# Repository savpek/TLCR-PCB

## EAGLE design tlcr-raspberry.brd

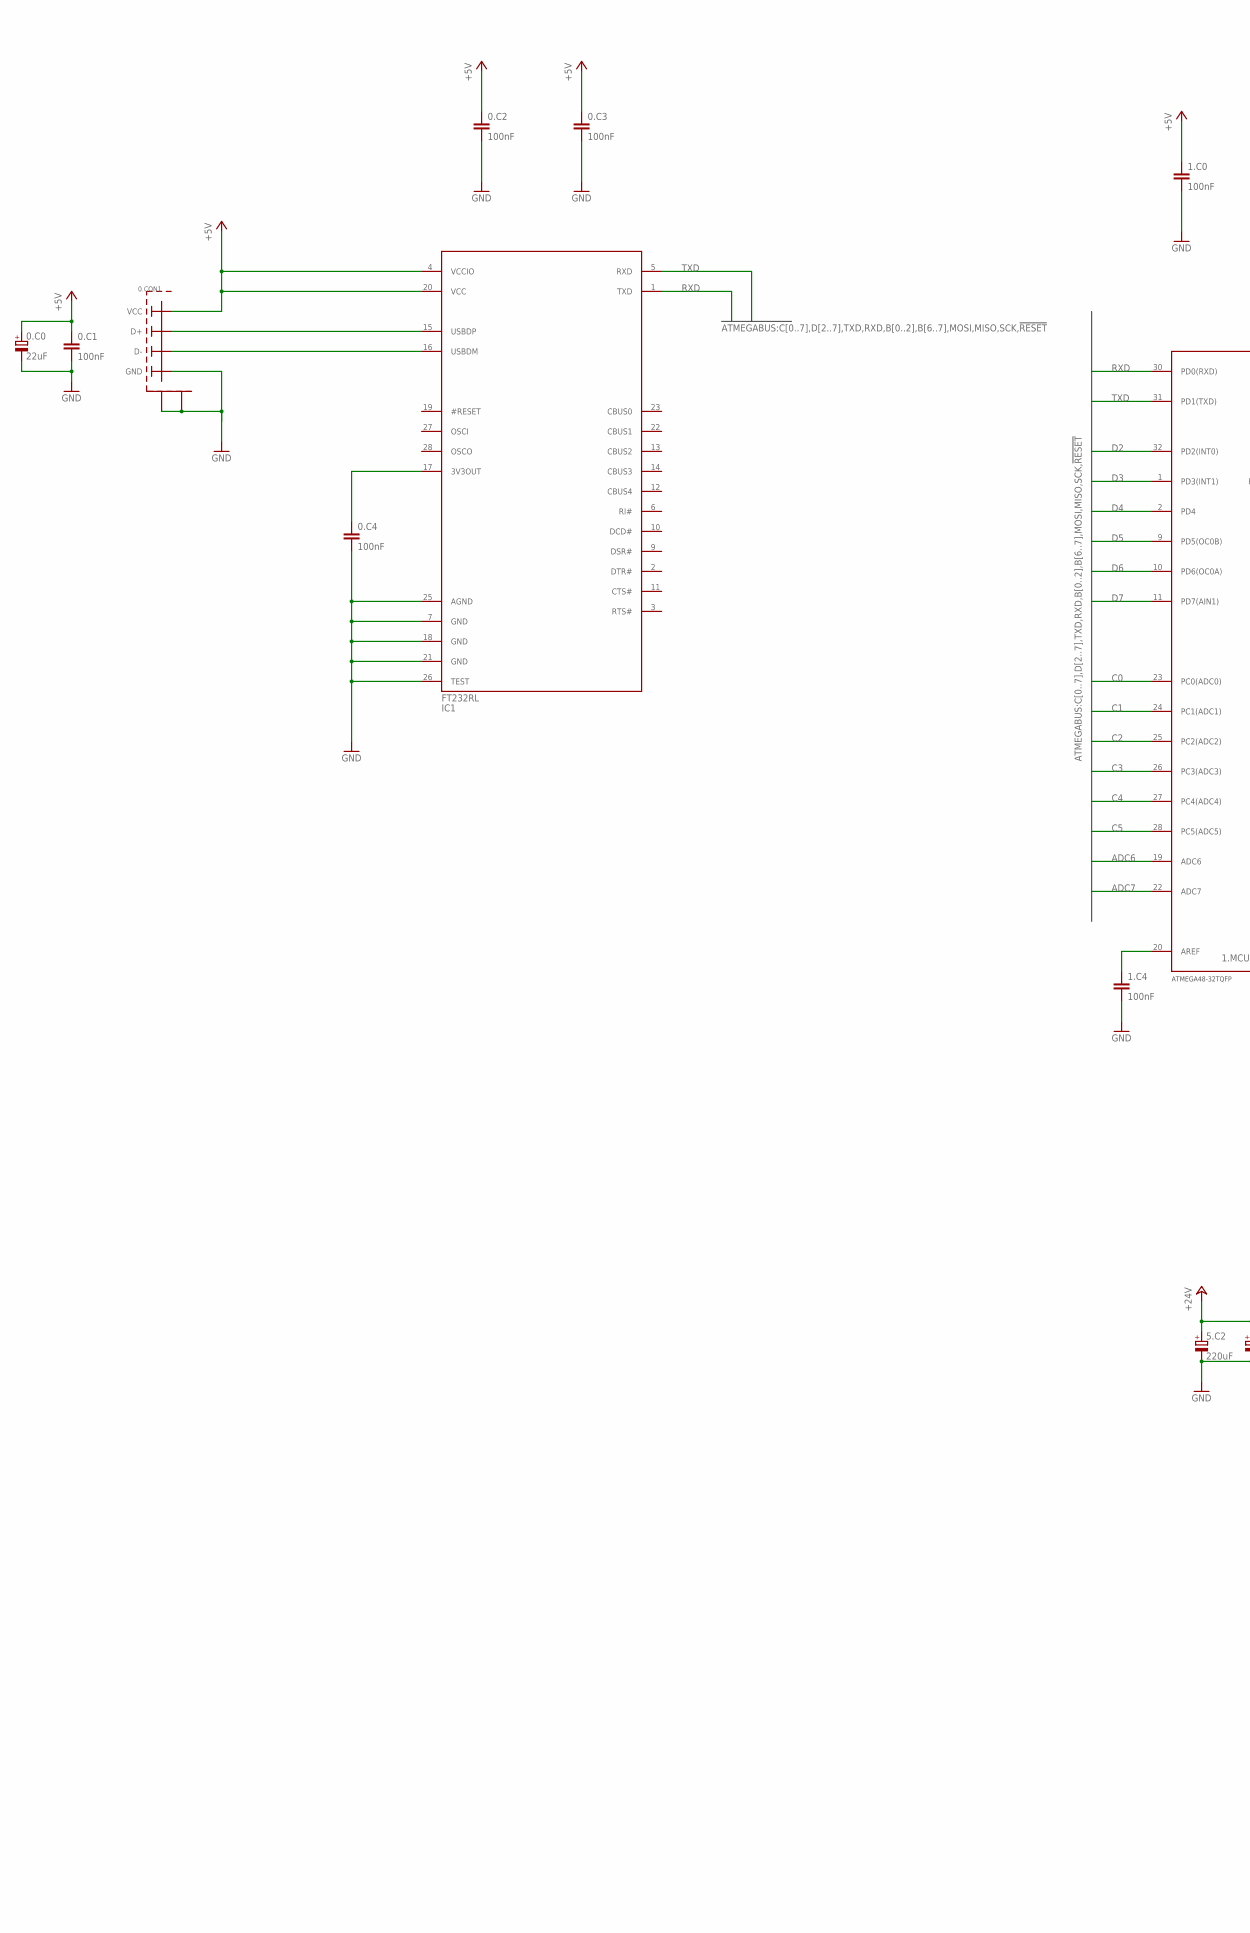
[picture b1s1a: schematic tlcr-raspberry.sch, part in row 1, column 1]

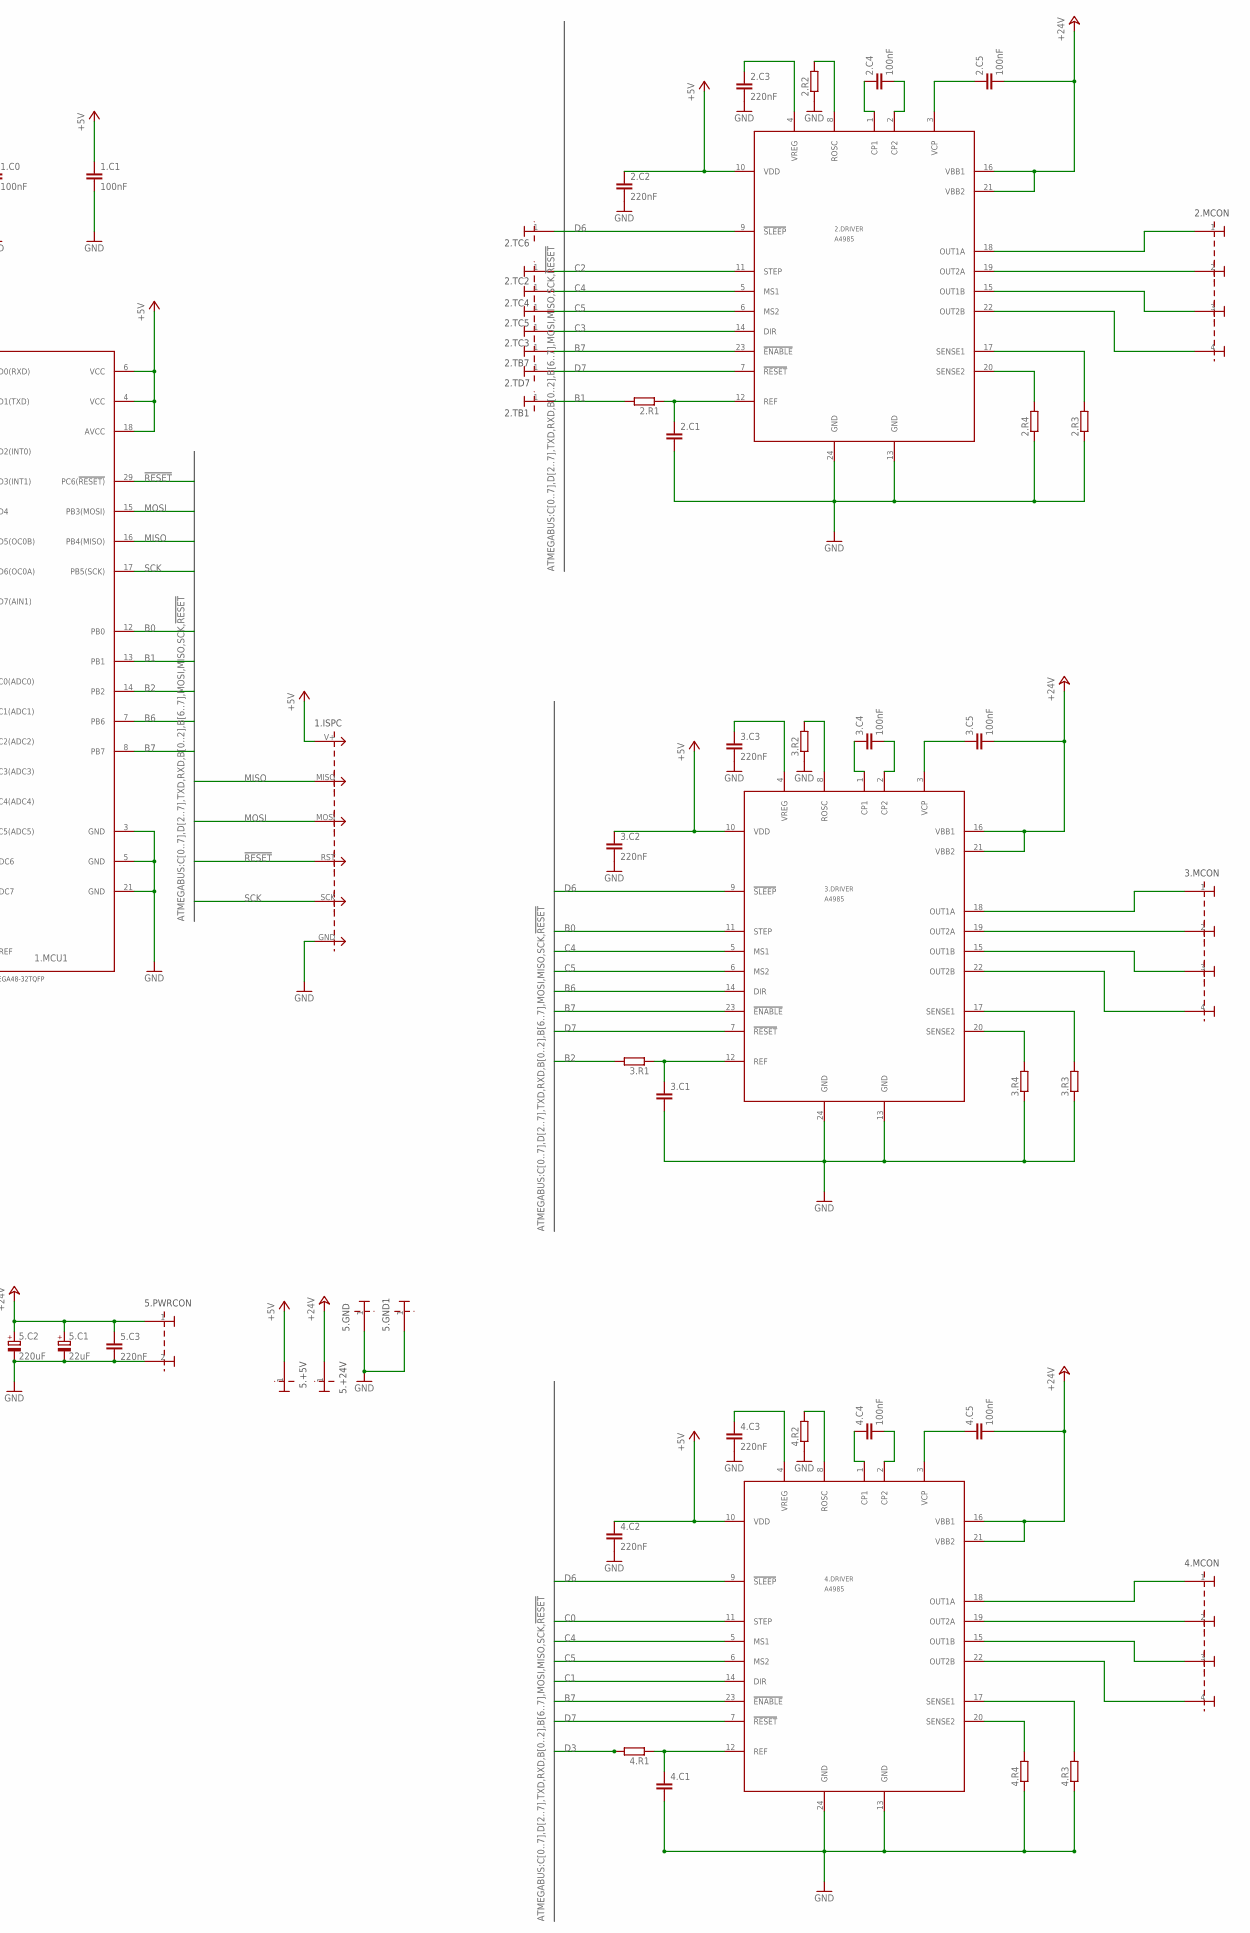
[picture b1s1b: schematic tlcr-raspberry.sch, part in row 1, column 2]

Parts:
0.C0: 22uF; E1.5-5
0.C1, 0.C2, 0.C3, 0.C4, 1.C0, 1.C1, 1.C4, 2.C4, 2.C5, 3.C4, 3.C5, 4.C4, 4.C5: 100nF; C0805
0.CON1: USB-BWUERTH-ELECTRONIC-USB-B; USB-B-THROUGH-HOLE
1.ISPC: CONNECTOR_6PIN2X3_ISP; 2X3_ISP
1.MCU1: ATMEGA48-20PU-32TQFPTQFP32; TQFP32-08
2.C1, 3.C1, 4.C1: C-EUC0805; C0805
2.C2, 2.C3, 3.C2, 3.C3, 4.C2, 4.C3, 5.C3: 220nF; C0805
2.DRIVER, 3.DRIVER, 4.DRIVER: A4985; SSOP24
2.MCON, 3.MCON, 4.MCON: CONNECTOR_4PIN; 1X4_GENERIC
2.R1, 2.R2, 3.R1, 3.R2, 4.R1, 4.R2: R-EU_R0805; R0805
2.R3, 2.R4, 3.R3, 3.R4, 4.R3, 4.R4: R-EU_R2010; R2010
2.TB1, 2.TB7, 2.TC2, 2.TC3, 2.TC4, 2.TC5, 2.TC6, 2.TD7, 5.+5V, 5.+24V, 5.GND, 5.GND1: CONNECTOR_1PIN1X1_HEADER; 1X1_GENERIC
5.C1: 22uF; 140CLH-0810
5.C2: 220uF; 140CLH-0810
5.PWRCON: CONNECTOR_2PIN1X2_WIRE; 1X2_WIRE
IC1: FT232RL; SSOP28

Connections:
!RESET: 1.ISPC.RST, 1.MCU1.29 (PC6(!RESET))
+5V: 0.C0.+, 0.C1.1, 0.C2.1, 0.C3.1, 0.CON1.VCC, 1.C0.1, 1.C1.1, 1.ISPC.V+, 1.MCU1.4 (VCC), 1.MCU1.6 (VCC), 1.MCU1.18 (AVCC), 2.C2.1, 2.DRIVER.10 (VDD), 3.C2.1, 3.DRIVER.10 (VDD), 4.C2.1, 4.DRIVER.10 (VDD), 5.+5V.1, IC1.4 (VCCIO), IC1.20 (VCC)
+24V: 2.C5.2, 2.DRIVER.16 (VBB1), 2.DRIVER.21 (VBB2), 3.C5.2, 3.DRIVER.16 (VBB1), 3.DRIVER.21 (VBB2), 4.C5.2, 4.DRIVER.16 (VBB1), 4.DRIVER.21 (VBB2), 5.+24V.1, 5.C1.+, 5.C2.+, 5.C3.1, 5.PWRCON.1
ADC6: 1.MCU1.19 (ADC6)
ADC7: 1.MCU1.22 (ADC7)
B0: 1.MCU1.12 (PB0), 3.DRIVER.11 (STEP)
B1: 1.MCU1.13 (PB1), 2.R1.2, 2.TB1.1
B2: 1.MCU1.14 (PB2), 3.R1.2
B6: 1.MCU1.7 (PB6), 3.DRIVER.14 (DIR)
B7: 1.MCU1.8 (PB7), 2.DRIVER.23 (!ENABLE), 2.TB7.1, 3.DRIVER.23 (!ENABLE), 4.DRIVER.23 (!ENABLE)
C0: 1.MCU1.23 (PC0(ADC0)), 4.DRIVER.11 (STEP)
C1: 1.MCU1.24 (PC1(ADC1)), 4.DRIVER.14 (DIR)
C2: 1.MCU1.25 (PC2(ADC2)), 2.DRIVER.11 (STEP), 2.TC2.1
C3: 1.MCU1.26 (PC3(ADC3)), 2.DRIVER.14 (DIR), 2.TC3.1
C4: 1.MCU1.27 (PC4(ADC4)), 2.DRIVER.5 (MS1), 2.TC4.1, 3.DRIVER.5 (MS1), 4.DRIVER.5 (MS1)
C5: 1.MCU1.28 (PC5(ADC5)), 2.DRIVER.6 (MS2), 2.TC5.1, 3.DRIVER.6 (MS2), 4.DRIVER.6 (MS2)
D2: 1.MCU1.32 (PD2(INT0))
D3: 1.MCU1.1 (PD3(INT1)), 4.R1.2
D4: 1.MCU1.2 (PD4)
D5: 1.MCU1.9 (PD5(OC0B))
D6: 1.MCU1.10 (PD6(OC0A)), 2.DRIVER.9 (!SLEEP), 2.TC6.1, 3.DRIVER.9 (!SLEEP), 4.DRIVER.9 (!SLEEP)
D7: 1.MCU1.11 (PD7(AIN1)), 2.DRIVER.7 (!RESET), 2.TD7.1, 3.DRIVER.7 (!RESET), 4.DRIVER.7 (!RESET)
GND: 0.C0.-, 0.C1.2, 0.C2.2, 0.C3.2, 0.C4.2, 0.CON1.GND, 0.CON1.SHIELD, 0.CON1.SHIELD@2 (SHIELD), 1.C0.2, 1.C1.2, 1.C4.2, 1.ISPC.GND, 1.MCU1.3 (GND), 1.MCU1.5 (GND), 1.MCU1.21 (GND), 2.C1.2, 2.C2.2, 2.C3.2, 2.DRIVER.13 (GND), 2.DRIVER.24 (GND), 2.R2.1, 2.R3.1, 2.R4.1, 3.C1.2, 3.C2.2, 3.C3.2, 3.DRIVER.13 (GND), 3.DRIVER.24 (GND), 3.R2.1, 3.R3.1, 3.R4.1, 4.C1.2, 4.C2.2, 4.C3.2, 4.DRIVER.13 (GND), 4.DRIVER.24 (GND), 4.R2.1, 4.R3.1, 4.R4.1, 5.C1.-, 5.C2.-, 5.C3.2, 5.GND.1, 5.GND1.1, 5.PWRCON.2, IC1.7 (GND), IC1.18 (GND), IC1.21 (GND), IC1.25 (AGND), IC1.26 (TEST)
MISO: 1.ISPC.MISO, 1.MCU1.16 (PB4(MISO))
MOSI: 1.ISPC.MOSI, 1.MCU1.15 (PB3(MOSI))
unnamed: 1.C4.1, 1.MCU1.20 (AREF)
unnamed: 2.C3.1, 2.DRIVER.4 (VREG)
unnamed: 0.CON1.D+, IC1.15 (USBDP)
unnamed: 0.CON1.D-, IC1.16 (USBDM)
unnamed: 2.C4.1, 2.DRIVER.1 (CP1)
unnamed: 2.C4.2, 2.DRIVER.2 (CP2)
unnamed: 0.C4.1, IC1.17 (3V3OUT)
unnamed: 2.C5.1, 2.DRIVER.3 (VCP)
unnamed: 3.C3.1, 3.DRIVER.4 (VREG)
unnamed: 2.DRIVER.18 (OUT1A), 2.MCON.1
unnamed: 2.DRIVER.19 (OUT2A), 2.MCON.2
unnamed: 2.DRIVER.15 (OUT1B), 2.MCON.3
unnamed: 2.DRIVER.22 (OUT2B), 2.MCON.4
unnamed: 2.DRIVER.17 (SENSE1), 2.R3.2
unnamed: 2.DRIVER.20 (SENSE2), 2.R4.2
unnamed: 3.C4.1, 3.DRIVER.1 (CP1)
unnamed: 3.C4.2, 3.DRIVER.2 (CP2)
unnamed: 2.DRIVER.8 (ROSC), 2.R2.2
unnamed: 3.C5.1, 3.DRIVER.3 (VCP)
unnamed: 3.DRIVER.18 (OUT1A), 3.MCON.1
unnamed: 3.DRIVER.19 (OUT2A), 3.MCON.2
unnamed: 3.DRIVER.15 (OUT1B), 3.MCON.3
unnamed: 3.DRIVER.22 (OUT2B), 3.MCON.4
unnamed: 3.DRIVER.17 (SENSE1), 3.R3.2
unnamed: 3.DRIVER.20 (SENSE2), 3.R4.2
unnamed: 3.DRIVER.8 (ROSC), 3.R2.2
unnamed: 4.C3.1, 4.DRIVER.4 (VREG)
unnamed: 4.C4.1, 4.DRIVER.1 (CP1)
unnamed: 4.C4.2, 4.DRIVER.2 (CP2)
unnamed: 4.C5.1, 4.DRIVER.3 (VCP)
unnamed: 4.DRIVER.18 (OUT1A), 4.MCON.1
unnamed: 4.DRIVER.19 (OUT2A), 4.MCON.2
unnamed: 4.DRIVER.15 (OUT1B), 4.MCON.3
unnamed: 4.DRIVER.22 (OUT2B), 4.MCON.4
unnamed: 4.DRIVER.17 (SENSE1), 4.R3.2
unnamed: 4.DRIVER.20 (SENSE2), 4.R4.2
unnamed: 4.DRIVER.8 (ROSC), 4.R2.2
unnamed: 3.C1.1, 3.DRIVER.12 (REF), 3.R1.1
unnamed: 4.C1.1, 4.DRIVER.12 (REF), 4.R1.1
unnamed: 2.C1.1, 2.DRIVER.12 (REF), 2.R1.1
RXD: 1.MCU1.30 (PD0(RXD)), IC1.1 (TXD)
SCK: 1.ISPC.SCK, 1.MCU1.17 (PB5(SCK))
TXD: 1.MCU1.31 (PD1(TXD)), IC1.5 (RXD)

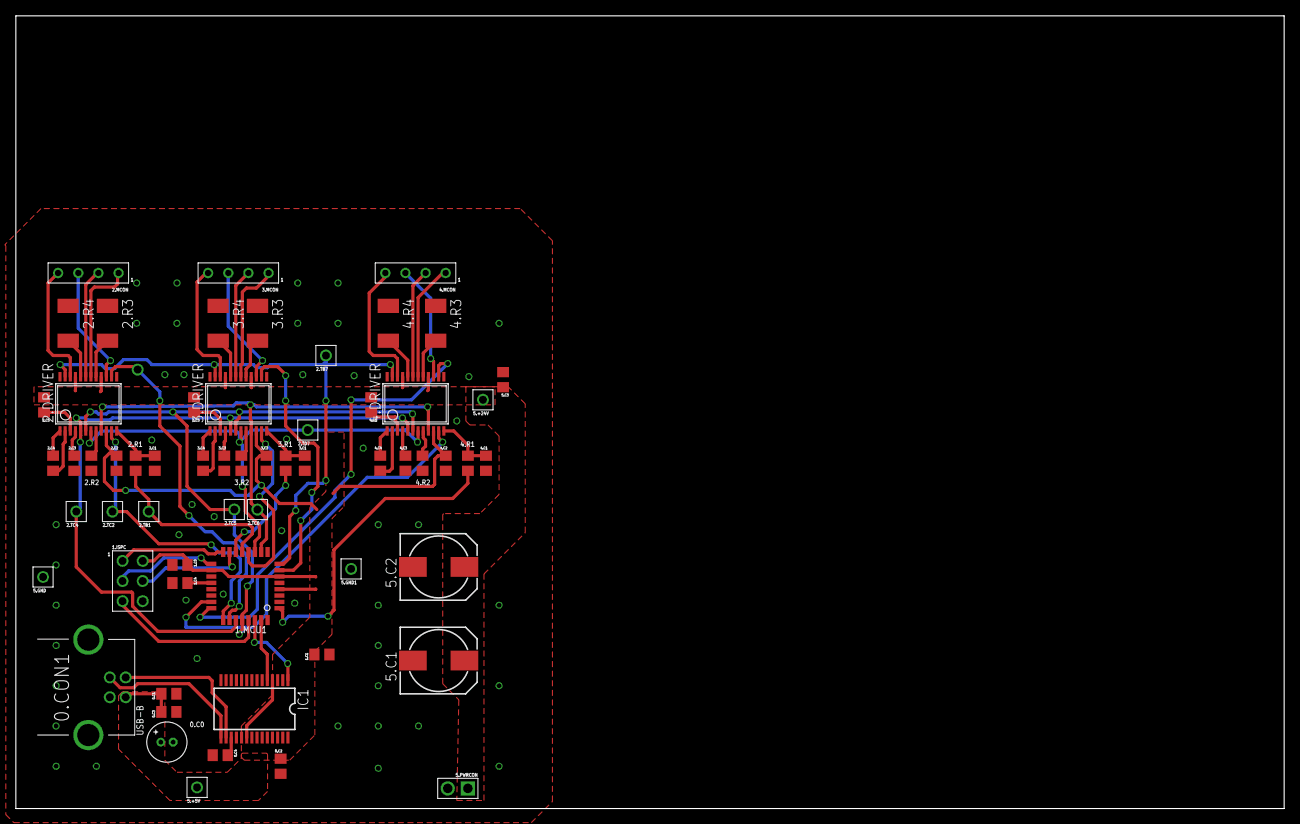
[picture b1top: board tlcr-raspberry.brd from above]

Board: 2 copper layers, 160.0 x 100.0 mm, 61 parts (1 on the bottom side), 63 nets.

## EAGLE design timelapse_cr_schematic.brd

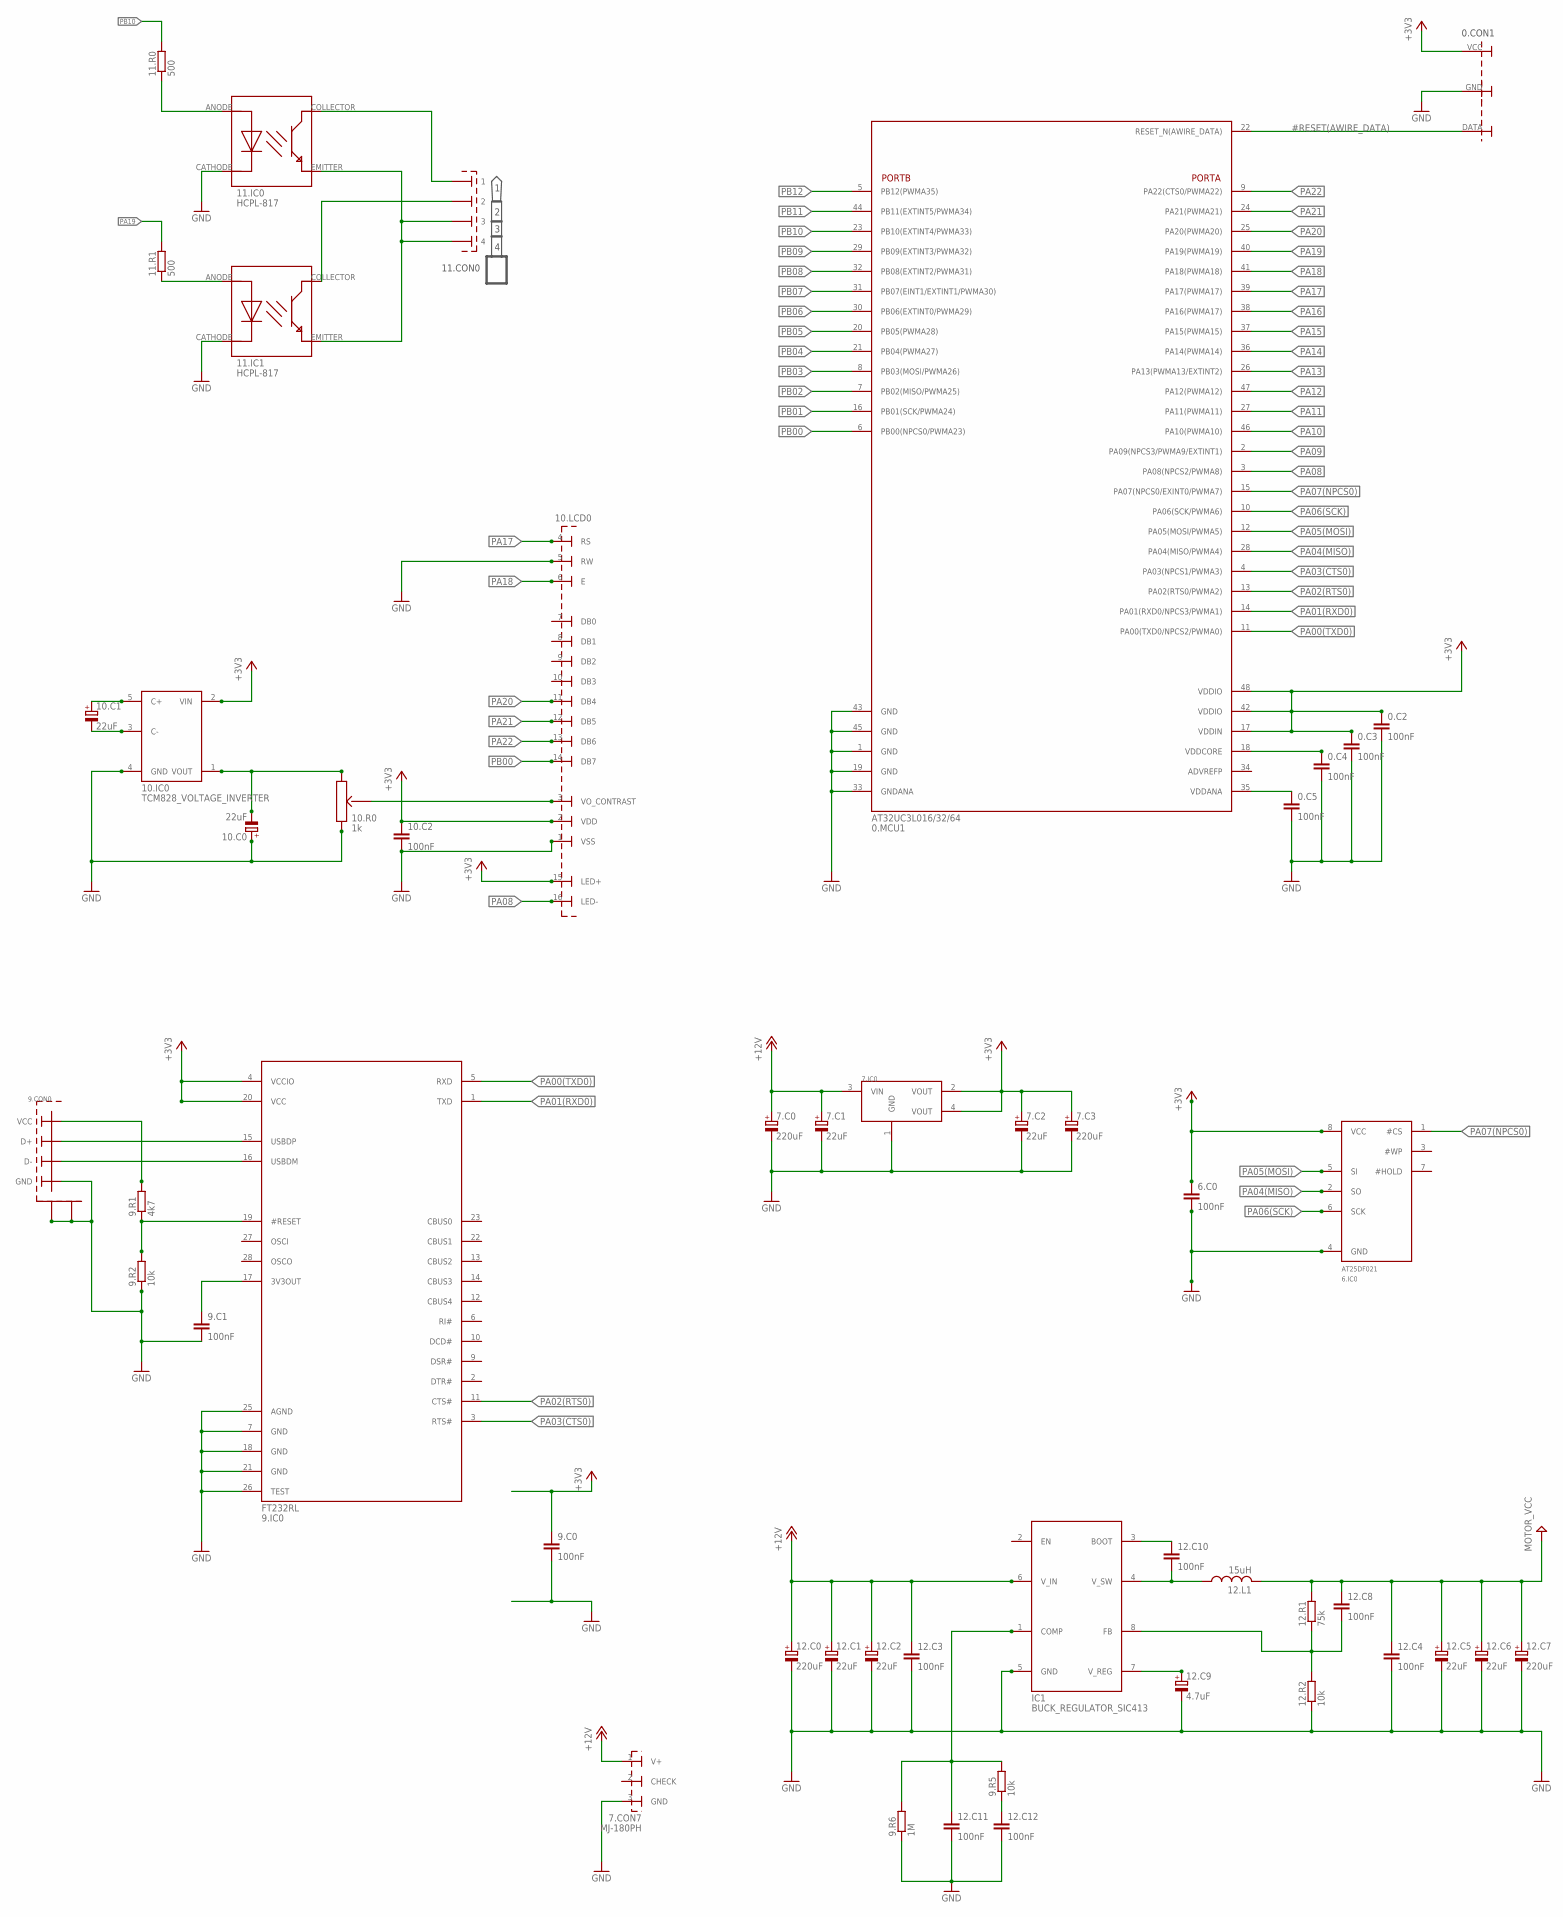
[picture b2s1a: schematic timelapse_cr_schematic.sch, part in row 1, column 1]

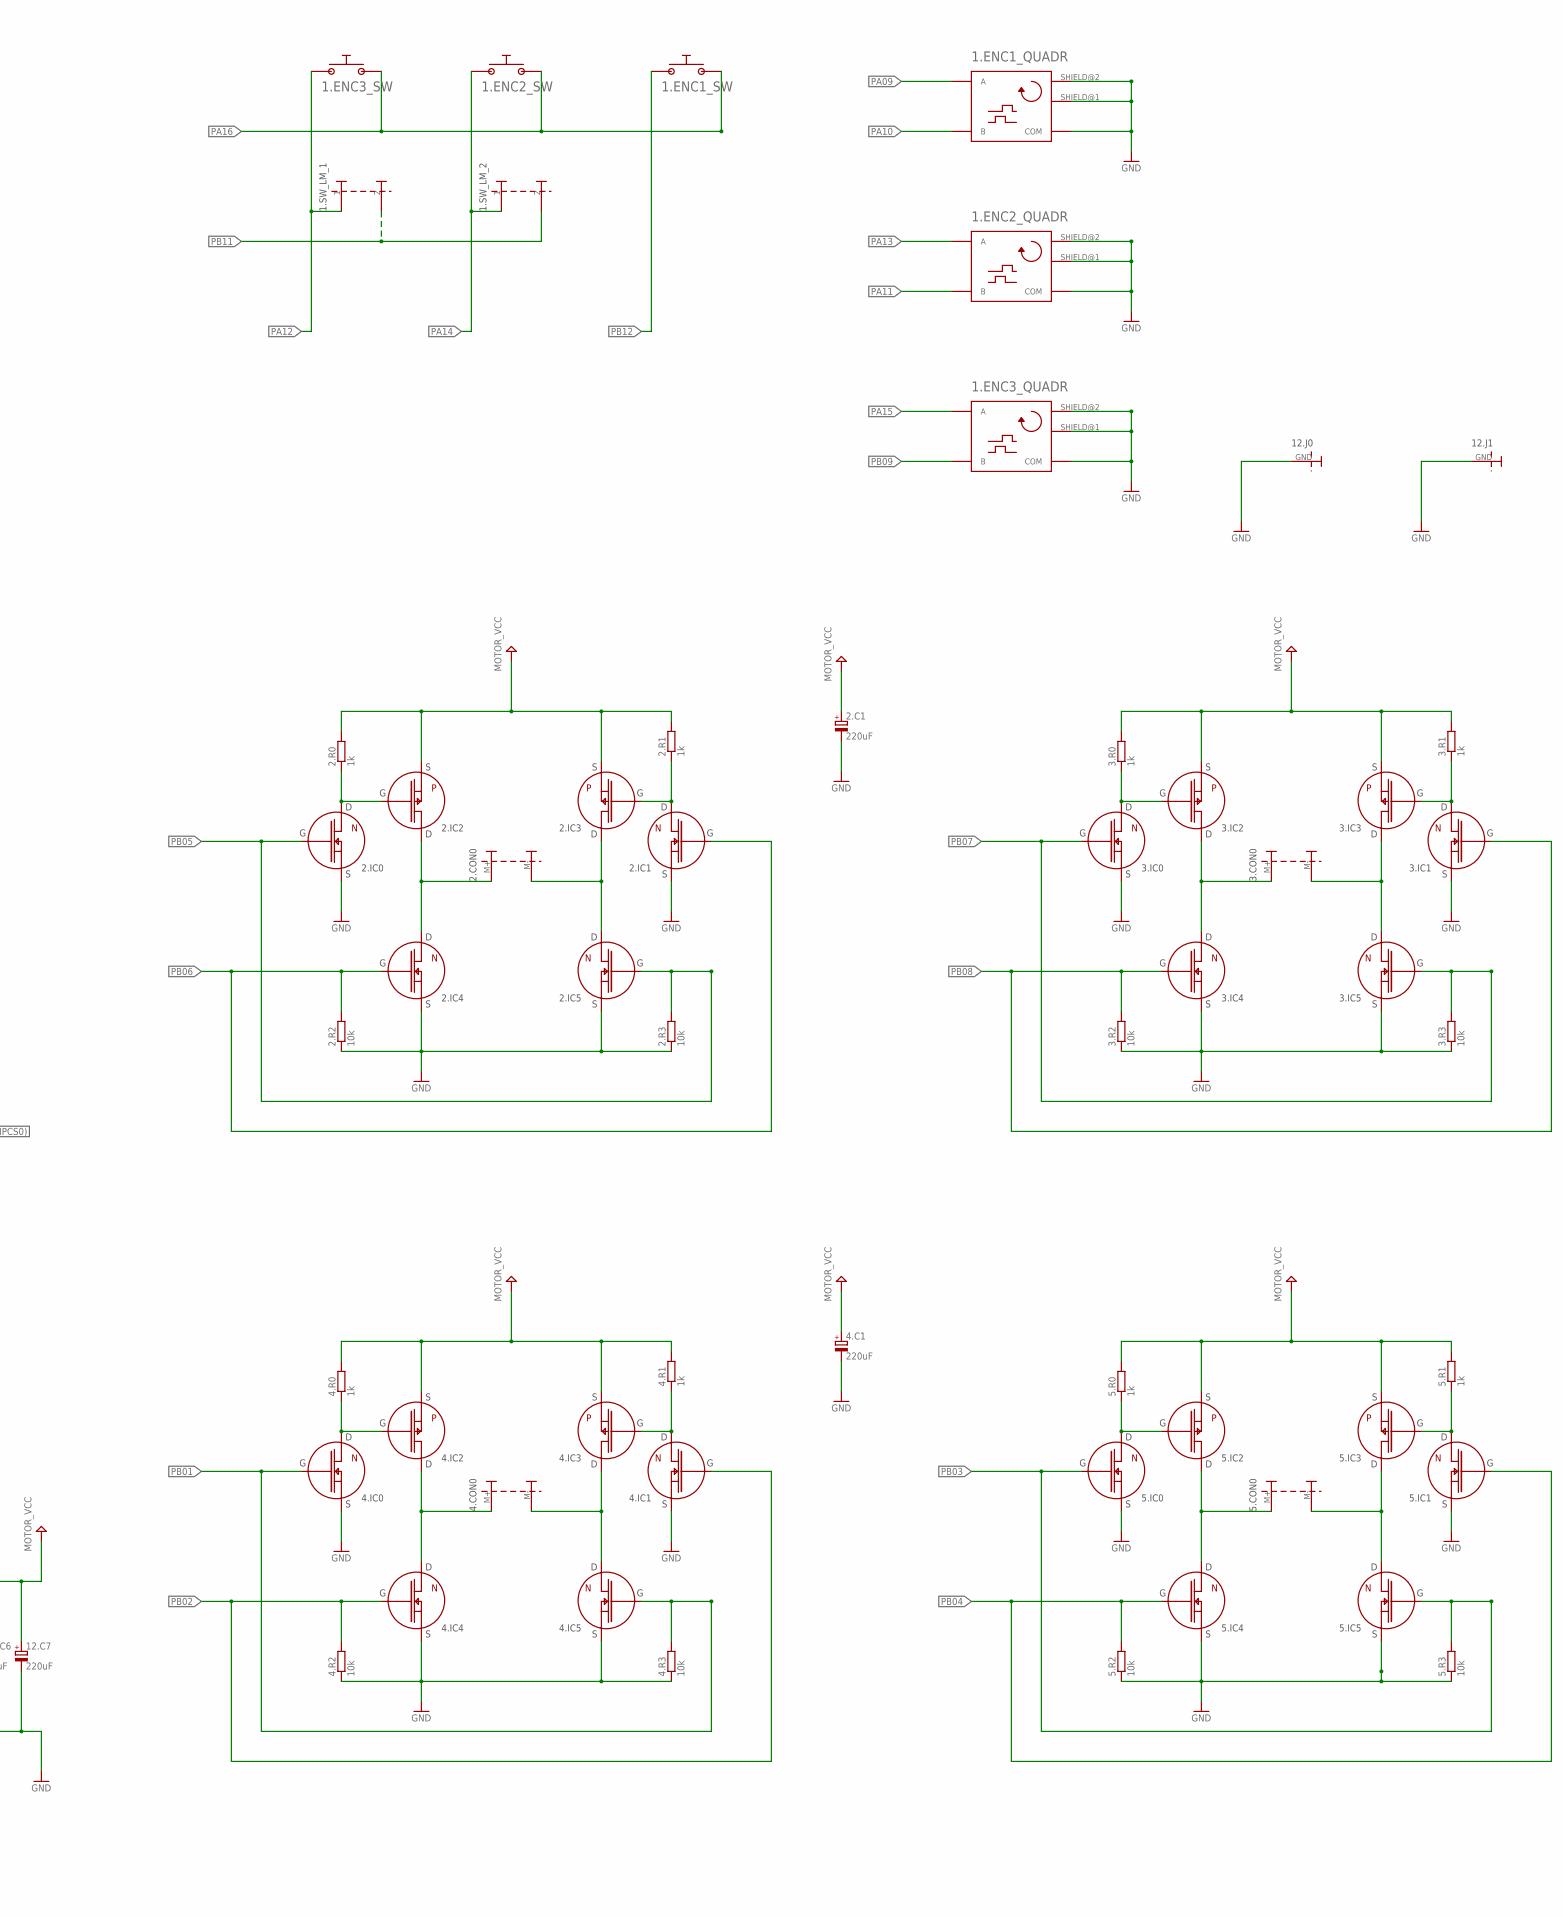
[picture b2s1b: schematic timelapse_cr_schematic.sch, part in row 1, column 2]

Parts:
0.C2, 0.C3, 0.C4, 0.C5, 6.C0, 9.C0, 9.C1, 10.C2, 12.C3, 12.C4, 12.C8, 12.C10, 12.C11, 12.C12: 100nF; C0805
0.CON1: CONNECTOR_3PINAWIRE; 1X3_AWIRE
0.MCU1: AT32UCL016/32/64_TQFP48; TQFP48
1.ENC1, 1.ENC2, 1.ENC3: ENCODER_QUADRATE_WITH_BUTTON_ENCODER_PEC11-4XXXF-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; ENCODER_PEC11-4XXXF-SXXXX
1.SW_LM_1, 1.SW_LM_2: CONNECTOR_2PIN; 1X2_WIRE
2.C1, 4.C1, 7.C0, 7.C3, 12.C0, 12.C7: 220uF; E3,5-8
2.CON0, 3.CON0, 4.CON0, 5.CON0: CONNECTOR_2PIN1X2_MOTOR_COIL; 1X2_MOTOR_COIL_CONNECTOR
2.IC0, 2.IC1, 3.IC0, 3.IC1, 4.IC0, 4.IC1, 5.IC0, 5.IC1: N_MOSFET_TSM2N7002; SOT23
2.IC2, 2.IC3, 3.IC2, 3.IC3, 4.IC2, 4.IC3, 5.IC2, 5.IC3: P_MOSFET_NX2301P; SOT23
2.IC4, 2.IC5, 3.IC4, 3.IC5, 4.IC4, 4.IC5, 5.IC4, 5.IC5: N_MOSFET_PMV16UN; SOT23
2.R0, 2.R1, 3.R0, 3.R1, 4.R0, 4.R1, 5.R0, 5.R1: 1k; R0805
2.R2, 2.R3, 3.R2, 3.R3, 4.R2, 4.R3, 5.R2, 5.R3, 9.R2, 9.R5, 12.R2: 10k; R0805
6.IC0: FLASH_AT25DF021_SO8; SO8
7.C1, 7.C2, 10.C0, 10.C1, 12.C1, 12.C2, 12.C5, 12.C6: 22uF; E1.5-5
7.CON7: MJ-180PH
7.IC0: REGULATOR_AP1117E33G-13; SOT223
9.CON0: USB-BWUERTH-ELECTRONIC-USB-B; USB-B-THROUGH-HOLE
9.IC0: FT232RL; SSOP28
9.R1: 4k7; R0805
9.R6: 1M; R0805
10.IC0: TCM828_VOLTAGE_INVERTER; SOT23-5L
10.LCD0: LCD_WITH_COMMON_INTERFACE_FDCC0802C-NSWBBH-91LE; LCD_FDCC0802C-NSWBBH-91LE
10.R0: 1k; CT6V
11.CON0: 2.5MM-JACK-STEREO-CONNECTOR; PSG01539
11.IC0, 11.IC1: HCPL-817; HPCL-817
11.R0, 11.R1: 500; R0805
12.C9: 4.7uF; E1.5-5
12.J0, 12.J1: CONNECTOR_1PINGND_PIN; 1X1_GND_PIN
12.L1: 15uH; INDUCTOR_MCBFS7330
12.R1: 75k; R0805
IC1: BUCK_REGULATOR_SIC413; SO8

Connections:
#RESET(AWIRE_DATA): 0.CON1.DATA, 0.MCU1.22 (RESET_N(AWIRE_DATA))
+3V3: 0.C2.1, 0.C3.1, 0.CON1.VCC, 0.MCU1.17 (VDDIN), 0.MCU1.42 (VDDIO), 0.MCU1.48 (VDDIO), 6.C0.1, 6.IC0.8 (VCC), 7.C2.+, 7.C3.+, 7.IC0.2 (VOUT), 7.IC0.4 (VOUT), 9.C0.1, 9.IC0.4 (VCCIO), 9.IC0.20 (VCC), 10.C2.1, 10.IC0.2 (VIN), 10.LCD0.2 (VDD), 10.LCD0.15 (LED+)
+12V: 7.C0.+, 7.C1.+, 7.CON7.1 (V+), 7.IC0.3 (VIN), 12.C0.+, 12.C1.+, 12.C2.+, 12.C3.1, IC1.6 (V_IN)
GND: 0.C2.2, 0.C3.2, 0.C4.2, 0.C5.2, 0.CON1.GND, 0.MCU1.1 (GND), 0.MCU1.19 (GND), 0.MCU1.33 (GNDANA), 0.MCU1.43 (GND), 0.MCU1.45 (GND), 1.ENC1.COMMON (COM), 1.ENC1.SHIELD@1 (SHIELD), 1.ENC1.SHIELD@2 (SHIELD), 1.ENC2.COMMON (COM), 1.ENC2.SHIELD@1 (SHIELD), 1.ENC2.SHIELD@2 (SHIELD), 1.ENC3.COMMON (COM), 1.ENC3.SHIELD@1 (SHIELD), 1.ENC3.SHIELD@2 (SHIELD), 2.C1.-, 2.IC0.2 (S), 2.IC1.2 (S), 2.IC4.2 (S), 2.IC5.2 (S), 2.R2.1, 2.R3.1, 3.IC0.2 (S), 3.IC1.2 (S), 3.IC4.2 (S), 3.IC5.2 (S), 3.R2.1, 3.R3.1, 4.C1.-, 4.IC0.2 (S), 4.IC1.2 (S), 4.IC4.2 (S), 4.IC5.2 (S), 4.R2.1, 4.R3.1, 5.IC0.2 (S), 5.IC1.2 (S), 5.IC4.2 (S), 5.IC5.2 (S), 5.R2.1, 5.R3.1, 6.C0.2, 6.IC0.4 (GND), 7.C0.-, 7.C1.-, 7.C2.-, 7.C3.-, 7.CON7.3 (GND), 7.IC0.1 (GND), 9.C0.2, 9.C1.2, 9.CON0.GND, 9.CON0.SHIELD, 9.CON0.SHIELD@2 (SHIELD), 9.IC0.7 (GND), 9.IC0.18 (GND), 9.IC0.21 (GND), 9.IC0.25 (AGND), 9.IC0.26 (TEST), 9.R2.1, 9.R6.1, 10.C0.+, 10.C2.2, 10.IC0.4 (GND), 10.LCD0.1 (VSS), 10.LCD0.5 (RW), 10.R0.3, 11.IC0.CATHODE, 11.IC1.CATHODE, 12.C0.-, 12.C1.-, 12.C2.-, 12.C3.2, 12.C4.2, 12.C5.-, 12.C6.-, 12.C7.-, 12.C9.-, 12.C11.2, 12.C12.2, 12.J0.GND, 12.J1.GND, 12.R2.1, IC1.5 (GND)
MOTOR_VCC: 2.C1.+, 2.IC2.2 (S), 2.IC3.2 (S), 2.R0.2, 2.R1.2, 3.IC2.2 (S), 3.IC3.2 (S), 3.R0.2, 3.R1.2, 4.C1.+, 4.IC2.2 (S), 4.IC3.2 (S), 4.R0.2, 4.R1.2, 5.IC2.2 (S), 5.IC3.2 (S), 5.R0.2, 5.R1.2, 12.C4.1, 12.C5.+, 12.C6.+, 12.C7.+, 12.C8.1, 12.L1.P$2 (2), 12.R1.2
unnamed: 9.C1.1, 9.IC0.17 (3V3OUT)
unnamed: 2.IC0.3 (D), 2.IC2.1 (G), 2.R0.1
unnamed: 9.CON0.D-, 9.IC0.16 (USBDM)
unnamed: 9.CON0.D+, 9.IC0.15 (USBDP)
unnamed: 9.CON0.VCC, 9.R1.2
unnamed: 9.IC0.19 (#RESET), 9.R1.1, 9.R2.2
unnamed: 3.IC0.3 (D), 3.IC2.1 (G), 3.R0.1
unnamed: 2.IC1.3 (D), 2.IC3.1 (G), 2.R1.1
unnamed: 2.CON0.M-, 2.IC3.3 (D), 2.IC5.3 (D)
unnamed: 2.CON0.M+, 2.IC2.3 (D), 2.IC4.3 (D)
unnamed: 3.IC1.3 (D), 3.IC3.1 (G), 3.R1.1
unnamed: 3.CON0.M-, 3.IC3.3 (D), 3.IC5.3 (D)
unnamed: 10.LCD0.3 (VO_CONTRAST), 10.R0.2
unnamed: 3.CON0.M+, 3.IC2.3 (D), 3.IC4.3 (D)
unnamed: 11.CON0.1 (4), 11.CON0.4 (3), 11.IC0.EMITTER, 11.IC1.EMITTER
unnamed: 10.C1.+, 10.IC0.5 (C+)
unnamed: 10.C1.-, 10.IC0.3 (C-)
unnamed: 4.IC0.3 (D), 4.IC2.1 (G), 4.R0.1
unnamed: 4.IC1.3 (D), 4.IC3.1 (G), 4.R1.1
unnamed: 4.CON0.M-, 4.IC3.3 (D), 4.IC5.3 (D)
unnamed: 4.CON0.M+, 4.IC2.3 (D), 4.IC4.3 (D)
unnamed: 9.R5.2, 9.R6.2, 12.C11.1, IC1.1 (COMP)
unnamed: 10.C0.-, 10.IC0.1 (VOUT), 10.R0.1
unnamed: 5.IC0.3 (D), 5.IC2.1 (G), 5.R0.1
unnamed: 5.IC1.3 (D), 5.IC3.1 (G), 5.R1.1
unnamed: 5.CON0.M-, 5.IC3.3 (D), 5.IC5.3 (D)
unnamed: 5.CON0.M+, 5.IC2.3 (D), 5.IC4.3 (D)
unnamed: 0.C4.1, 0.MCU1.18 (VDDCORE)
unnamed: 12.C10.1, IC1.3 (BOOT)
unnamed: 12.C8.2, 12.R1.1, 12.R2.2, IC1.8 (FB)
unnamed: 11.CON0.3 (1), 11.IC0.COLLECTOR
unnamed: 12.C10.2, 12.L1.P$1 (1), IC1.4 (V_SW)
unnamed: 9.R5.1, 12.C12.1
unnamed: 11.CON0.2, 11.IC1.COLLECTOR
unnamed: 0.C5.1, 0.MCU1.35 (VDDANA)
unnamed: 12.C9.+, IC1.7 (V_REG)
unnamed: 11.IC0.ANODE, 11.R0.1
unnamed: 11.IC1.ANODE, 11.R1.1
PA00(TXD0): 0.MCU1.11 (PA00(TXD0/NPCS2/PWMA0)), 9.IC0.5 (RXD)
PA01(RXD0): 0.MCU1.14 (PA01(RXD0/NPCS3/PWMA1)), 9.IC0.1 (TXD)
PA02(RTS0): 0.MCU1.13 (PA02(RTS0/PWMA2)), 9.IC0.11 (CTS#)
PA03(CTS0): 0.MCU1.4 (PA03(NPCS1/PWMA3)), 9.IC0.3 (RTS#)
PA04(MISO): 0.MCU1.28 (PA04(MISO/PWMA4)), 6.IC0.2 (SO)
PA05(MOSI): 0.MCU1.12 (PA05(MOSI/PWMA5)), 6.IC0.5 (SI)
PA06(SCK): 0.MCU1.10 (PA06(SCK/PWMA6)), 6.IC0.6 (SCK)
PA07(NPCS0): 0.MCU1.15 (PA07(NPCS0/EXINT0/PWMA7)), 6.IC0.1 (#CS)
PA08: 0.MCU1.3 (PA08(NPCS2/PWMA8)), 10.LCD0.16 (LED-)
PA09: 0.MCU1.2 (PA09(NPCS3/PWMA9/EXTINT1)), 1.ENC1.A
PA10: 0.MCU1.46 (PA10(PWMA10)), 1.ENC1.B
PA11: 0.MCU1.27 (PA11(PWMA11)), 1.ENC2.B
PA12: 0.MCU1.47 (PA12(PWMA12)), 1.ENC3.SW1, 1.SW_LM_1.1
PA13: 0.MCU1.26 (PA13(PWMA13/EXTINT2)), 1.ENC2.A
PA14: 0.MCU1.36 (PA14(PWMA14)), 1.ENC2.SW1, 1.SW_LM_2.1
PA15: 0.MCU1.37 (PA15(PWMA15)), 1.ENC3.A
PA16: 0.MCU1.38 (PA16(PWMA17)), 1.ENC1.SW2, 1.ENC2.SW2, 1.ENC3.SW2
PA17: 0.MCU1.39 (PA17(PWMA17)), 10.LCD0.4 (RS)
PA18: 0.MCU1.41 (PA18(PWMA18)), 10.LCD0.6 (E)
PA19: 0.MCU1.40 (PA19(PWMA19)), 11.R1.2
PA20: 0.MCU1.25 (PA20(PWMA20)), 10.LCD0.11 (DB4)
PA21: 0.MCU1.24 (PA21(PWMA21)), 10.LCD0.12 (DB5)
PA22: 0.MCU1.9 (PA22(CTS0/PWMA22)), 10.LCD0.13 (DB6)
PB00: 0.MCU1.6 (PB00(NPCS0/PWMA23)), 10.LCD0.14 (DB7)
PB01: 0.MCU1.16 (PB01(SCK/PWMA24)), 4.IC0.1 (G), 4.IC5.1 (G), 4.R3.2
PB02: 0.MCU1.7 (PB02(MISO/PWMA25)), 4.IC1.1 (G), 4.IC4.1 (G), 4.R2.2
PB03: 0.MCU1.8 (PB03(MOSI/PWMA26)), 5.IC0.1 (G), 5.IC5.1 (G), 5.R3.2
PB04: 0.MCU1.21 (PB04(PWMA27)), 5.IC1.1 (G), 5.IC4.1 (G), 5.R2.2
PB05: 0.MCU1.20 (PB05(PWMA28)), 2.IC0.1 (G), 2.IC5.1 (G), 2.R3.2
PB06: 0.MCU1.30 (PB06(EXTINT0/PWMA29)), 2.IC1.1 (G), 2.IC4.1 (G), 2.R2.2
PB07: 0.MCU1.31 (PB07(EINT1/EXTINT1/PWMA30)), 3.IC0.1 (G), 3.IC5.1 (G), 3.R3.2
PB08: 0.MCU1.32 (PB08(EXTINT2/PWMA31)), 3.IC1.1 (G), 3.IC4.1 (G), 3.R2.2
PB09: 0.MCU1.29 (PB09(EXTINT3/PWMA32)), 1.ENC3.B
PB10: 0.MCU1.23 (PB10(EXTINT4/PWMA33)), 11.R0.2
PB11: 0.MCU1.44 (PB11(EXTINT5/PWMA34)), 1.SW_LM_1.2, 1.SW_LM_2.2
PB12: 0.MCU1.5 (PB12(PWMA35)), 1.ENC1.SW1

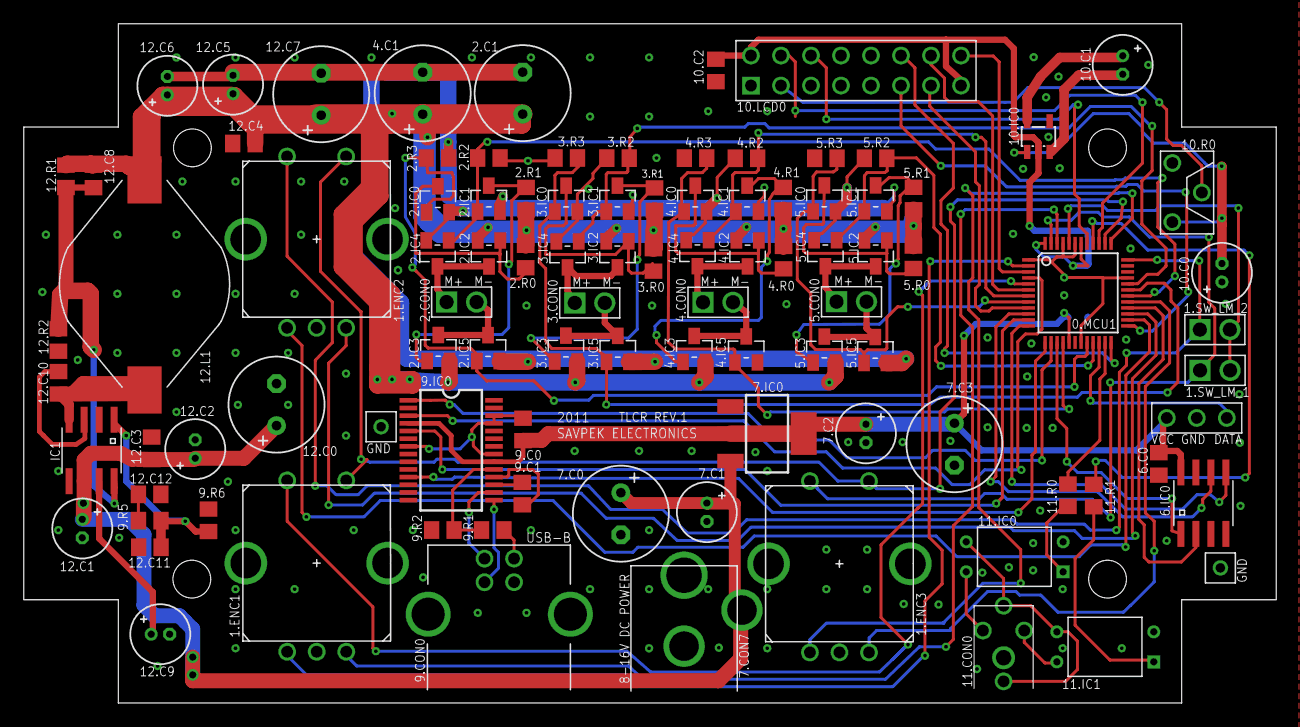
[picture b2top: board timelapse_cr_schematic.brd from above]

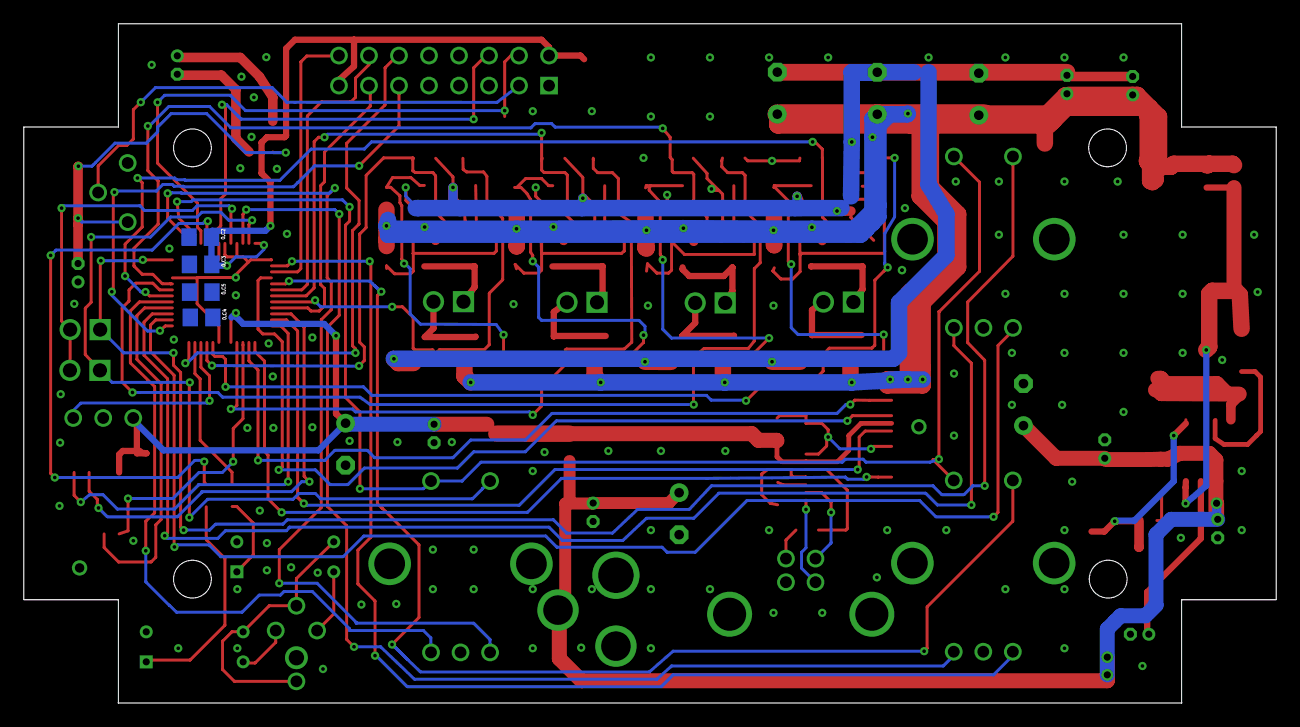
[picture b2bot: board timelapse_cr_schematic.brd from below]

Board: 2 copper layers, 106.0 x 57.5 mm, 103 parts (4 on the bottom side), 79 nets.
